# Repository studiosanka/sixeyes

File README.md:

# SixEyes

**A ~S$250 6-DOF robotic arm with 500 g @ 500 mm capability, designed to be built at home.**

SixEyes is an open-source 5-DOF arm plus a gripper, built from 3D-printed cycloidal gearboxes, NEMA17
stepper motors and a hand-solderable PCB. The ~S$250 figure is the whole-arm build budget (prints,
mechanics and electronics; power supply and computer excluded), and 500 g at 500 mm is the design target.

> **Work in progress.** The board design and PCB layout (v1.2) are finished but not yet built or tested. The firmware builds
> but has not run on hardware yet, and the printable parts and build guides are not published yet. Check the
> [status](#status) before you buy anything.

| Front | Back |
|:-:|:-:|
|  |  |

*3D render of the joint board on a NEMA 17 motor (the motor is drawn transparent). Left: the front. Right: the back, with the AS5600 encoder module and the four standoffs that carry the motor. The Super Mini and TMC2209 modules are not shown in their sockets.*

## What you will build

One **Universal Joint PCB** design (ESP32-C6 Super Mini, TMC2209 driver and AS5600 encoder as plug-in or
solder-on modules, fully through-hole) is built four times and linked by a CAN bus:

| Board | Populated | Role |
|---|---|---|
| Base | Stepper 1 driver, USB-C | Bus master, link to your computer |
| Shoulder L | Stepper 2A driver | CAN node |
| Shoulder R | Stepper 2B driver | CAN node, inverse-direction logic |
| Elbow | Stepper 3 driver, 3× servo headers (open-loop) | CAN node, closest to the wrist and gripper |

- **Bus:** CAN at 1 Mbps, a linear chain Base → Shoulder L → Shoulder R → Elbow.
- **Motors:** four NEMA17 (40 mm class) behind 1:25 printed cycloidal reductions. The shoulder uses two
  motors sharing one gearbox.
- **Feedback:** an AS5600 magnetic encoder reads a magnet on each motor shaft.

## Ways to drive the arm

The Base board has two links: **USB** to a computer and **Bluetooth** to a phone. Only one of them is in
control at a time, and the arm says which in every status message. That gives three modes:

| Mode | Who drives | Link | What it is for | Software to use |
|---|---|---|---|---|
| **1. Phone** | Your phone | Bluetooth | Move the gripper by moving your phone; record a movement and replay it, with no computer | [sixeyes-drive](https://github.com/studiosanka/sixeyes-drive) |
| **2. Phone, computer records** | Your phone | Bluetooth for the phone, USB for the computer | Record training data (joint positions and what the phone commanded) while a person teleoperates | [lerobot-sixeyes](https://github.com/studiosanka/lerobot-sixeyes) (listen-only), on top of [sixeyes-host](https://github.com/studiosanka/sixeyes-host) |
| **3. Computer** | A program on your computer | USB | Scripts, motion planning, or a trained AI policy driving the arm | [sixeyes-host](https://github.com/studiosanka/sixeyes-host) (Python), [sixeyes_ros2](https://github.com/studiosanka/sixeyes_ros2) (ROS 2 and MoveIt), [lerobot-sixeyes](https://github.com/studiosanka/lerobot-sixeyes) (LeRobot policy) |

The arm needs no computer for Mode 1. Every tool also has a **practice arm**, so you can try the software
before the hardware is built.

### Software repositories

| Repository | What it is | Used in mode |
|---|---|---|
| [sixeyes-host](https://github.com/studiosanka/sixeyes-host) | The USB protocol (version 1), a Python library, a simulated arm and the `sixeyes-bringup` tool (ports, home, jog, check encoders, monitor). Every other tool builds on it | 2, 3 (and the protocol for 1) |
| [sixeyes-drive](https://github.com/studiosanka/sixeyes-drive) | A web page for Chrome on an Android phone: hold a button and move the phone, record and replay | 1 |
| [lerobot-sixeyes](https://github.com/studiosanka/lerobot-sixeyes) | Plugins for [LeRobot](https://github.com/huggingface/lerobot): record data (Mode 2) and run a policy (Mode 3) | 2, 3 |
| [sixeyes_ros2](https://github.com/studiosanka/sixeyes_ros2) | ROS 2 and MoveIt control, in a mock arm, Gazebo or the real arm | 3 |
| [sixeyes_description](https://github.com/studiosanka/sixeyes_description) | The arm's shape and joint limits (URDF), shared by ROS 2 and the phone page. Placeholder numbers until the CAD is final | 1, 3 |

How the firmware in this repository fits in: it speaks the host protocol on both links
([`firmware/joint_node`](firmware/joint_node/docs/README.md)), arbitrates who is in control, and can store
motions on the arm itself. The Bluetooth service is described there. All of these repositories are
work in progress and **none has run on a real arm yet**; each one's README has its own status table.

## Start here

1. Read the [documentation index](docs/README.md) and follow the numbered guides.
2. The parts list with LCSC part numbers is [`hardware/pcb/bom/v1.2_BOM_LCSC.csv`](hardware/pcb/bom/v1.2_BOM_LCSC.csv).
3. The circuit and wiring are explained in the [PCB design reference](docs/reference/v1.2_PCB_Design_Reference.md).
4. The S$250 claim is checked line by line in the [budget](docs/reference/BUDGET.md).

## Repository map

```
hardware/    PCB (KiCad project, libraries, bill of materials), mechanical files, helper scripts
firmware/    joint_node: the code that runs on the four joint boards
docs/        build guides (start with docs/README.md) and reference documents
```

The software that talks to the arm lives in separate repositories under
[studiosanka](https://github.com/studiosanka); see [Ways to drive the arm](#ways-to-drive-the-arm).

Earlier generations of the project (Alpha and Beta boards, experiments) are kept for reference on the
`archive/dev-2026-10` branch.

## Status

| Part | State |
|---|---|
| Board design v1.2 (circuit, parts list) | ✅ written |
| KiCad schematic and PCB layout | ✅ v1.2 complete (checks clean, not yet built or tested) |
| Manufacturing files (Gerbers) | ✅ v1.2 in [`hardware/pcb/gerbers/`](hardware/pcb/gerbers/) |
| [Budget (S$250 claim)](docs/reference/BUDGET.md) | 🚧 being verified; S$186 priced at average survey prices, S$64 left for the mechanical parts |
| Firmware (`firmware/joint_node`) | 🚧 builds for all four board roles, with the host link, Bluetooth, homing and motion slots; not yet run on hardware |
| Host software (USB, phone, ROS 2, LeRobot) | 🚧 written in [separate repositories](#software-repositories); tested against practice arms only |
| CAN protocol | 🚧 draft |
| 3D-printable parts | ⬜ not yet published |
| Build guides | 🚧 outlines (overview and parts list drafted) |

## Contributing

See [CONTRIBUTING.md](CONTRIBUTING.md) for the usage terms and contribution policy.

## Licence

SixEyes uses three licences:

| | Licence |
|---|---|
| Firmware and software | [Apache 2.0](LICENSE) |
| Hardware designs (KiCad, Gerbers, STL) | [CERN-OHL-S-2.0](hardware/LICENSE) |
| Documentation | [CC-BY-4.0](docs/LICENSE) |

See [CONTRIBUTING.md](CONTRIBUTING.md) for what is required if you manufacture or sell hardware based on these
designs.

## AI assistance

The firmware, software and documentation in this repository were developed with AI assistance from
[Claude](https://www.anthropic.com/claude) (Anthropic) and [GitHub Copilot](https://github.com/features/copilot).
The designs, decisions and review are by the Studio Sanka team.

## Credits

| Role | Contributor |
|---|---|
| Project Lead | Vincent Santosa ([@markantosa](https://github.com/markantosa)) |
| Firmware & System Architecture | Vincent Santosa ([@markantosa](https://github.com/markantosa)) |
| Joint PCB Design (v1) and earlier Follower PCB Design | Vincent Santosa ([@markantosa](https://github.com/markantosa)) |
| Cycloidal Drive Design Lead | Chai ([@sevenovaa](https://github.com/sevenovaa)) |
| Leader PCB Design (Alpha/Beta, archived) | Audrey ([@odriyy](https://github.com/odriyy)) |
| Mechanical Design (cycloidal drive, original design) | Ren Jie ([@trenjie03](https://github.com/trenjie03)) |

## Contact

Bugs and questions: https://github.com/studiosanka/sixeyes/issues

---

Built by [Studio Sanka](https://github.com/studiosanka), a not-for-profit mechatronics design collaborative in
Singapore. **Last updated:** October 2026.

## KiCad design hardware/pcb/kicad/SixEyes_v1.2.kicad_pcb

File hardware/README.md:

# Hardware

Everything needed to build the electronics and the mechanics of the arm.

| Front | Back |
|:-:|:-:|
|  |  |

*3D renders of the joint board on a NEMA 17 motor (the motor is drawn transparent). Left: the front. Right: the back, with the AS5600 encoder module and the four standoffs that carry the motor. The Super Mini and TMC2209 modules are not shown in their sockets.*

| Folder | What is in it | Status |
|---|---|---|
| [`pcb/kicad/`](pcb/kicad/) | KiCad project for the joint board (open `SixEyes_v1.2.kicad_pro`) | ready (v1.2) |
| [`pcb/libraries/`](pcb/libraries/) | Symbols, footprints and 3D models the project uses (nothing to install) | ready |
| [`pcb/bom/`](pcb/bom/) | Bill of materials with LCSC part numbers | ready (v1.2) |
| [`bom/`](bom/) | Bill of materials for the whole arm (quantities and specs, no prices) | electronics ready, mechanical to come |
| [`pcb/drawings/`](pcb/drawings/) | Signed schematic and layout plots (PDF), v1.2 | ready |
| [`pcb/gerbers/`](pcb/gerbers/) | Files to send to a PCB manufacturer | ready (v1.2) |
| [`mechanical/stl/`](mechanical/stl/) | 3D-printable parts | coming soon |
| [`tools/`](tools/) | Scripts that generate the custom KiCad parts | for maintainers |

Open the KiCad project with KiCad 10. The project finds its libraries relative to itself.

The circuit is explained in the [PCB design reference](../docs/reference/v1.2_PCB_Design_Reference.md).

## A note on the tight placement

The components on this board are packed very tightly, and in a few places parts slightly overlap. That is deliberate: the aim was a small board that sits on the back of a NEMA 17 motor, made only of through-hole parts a beginner can solder, and kept neat. KiCad's courtyard checks are switched off for that reason, while every other check (clearance, shorts, hole spacing, edge distance, our own power and CAN rules) is clean. We are sorry if it makes review harder, and we hope you understand. See the [design reference](../docs/reference/v1.2_PCB_Design_Reference.md) for details.

## Licence

Hardware designs are licensed under CERN-OHL-S-2.0, see [LICENSE](LICENSE).

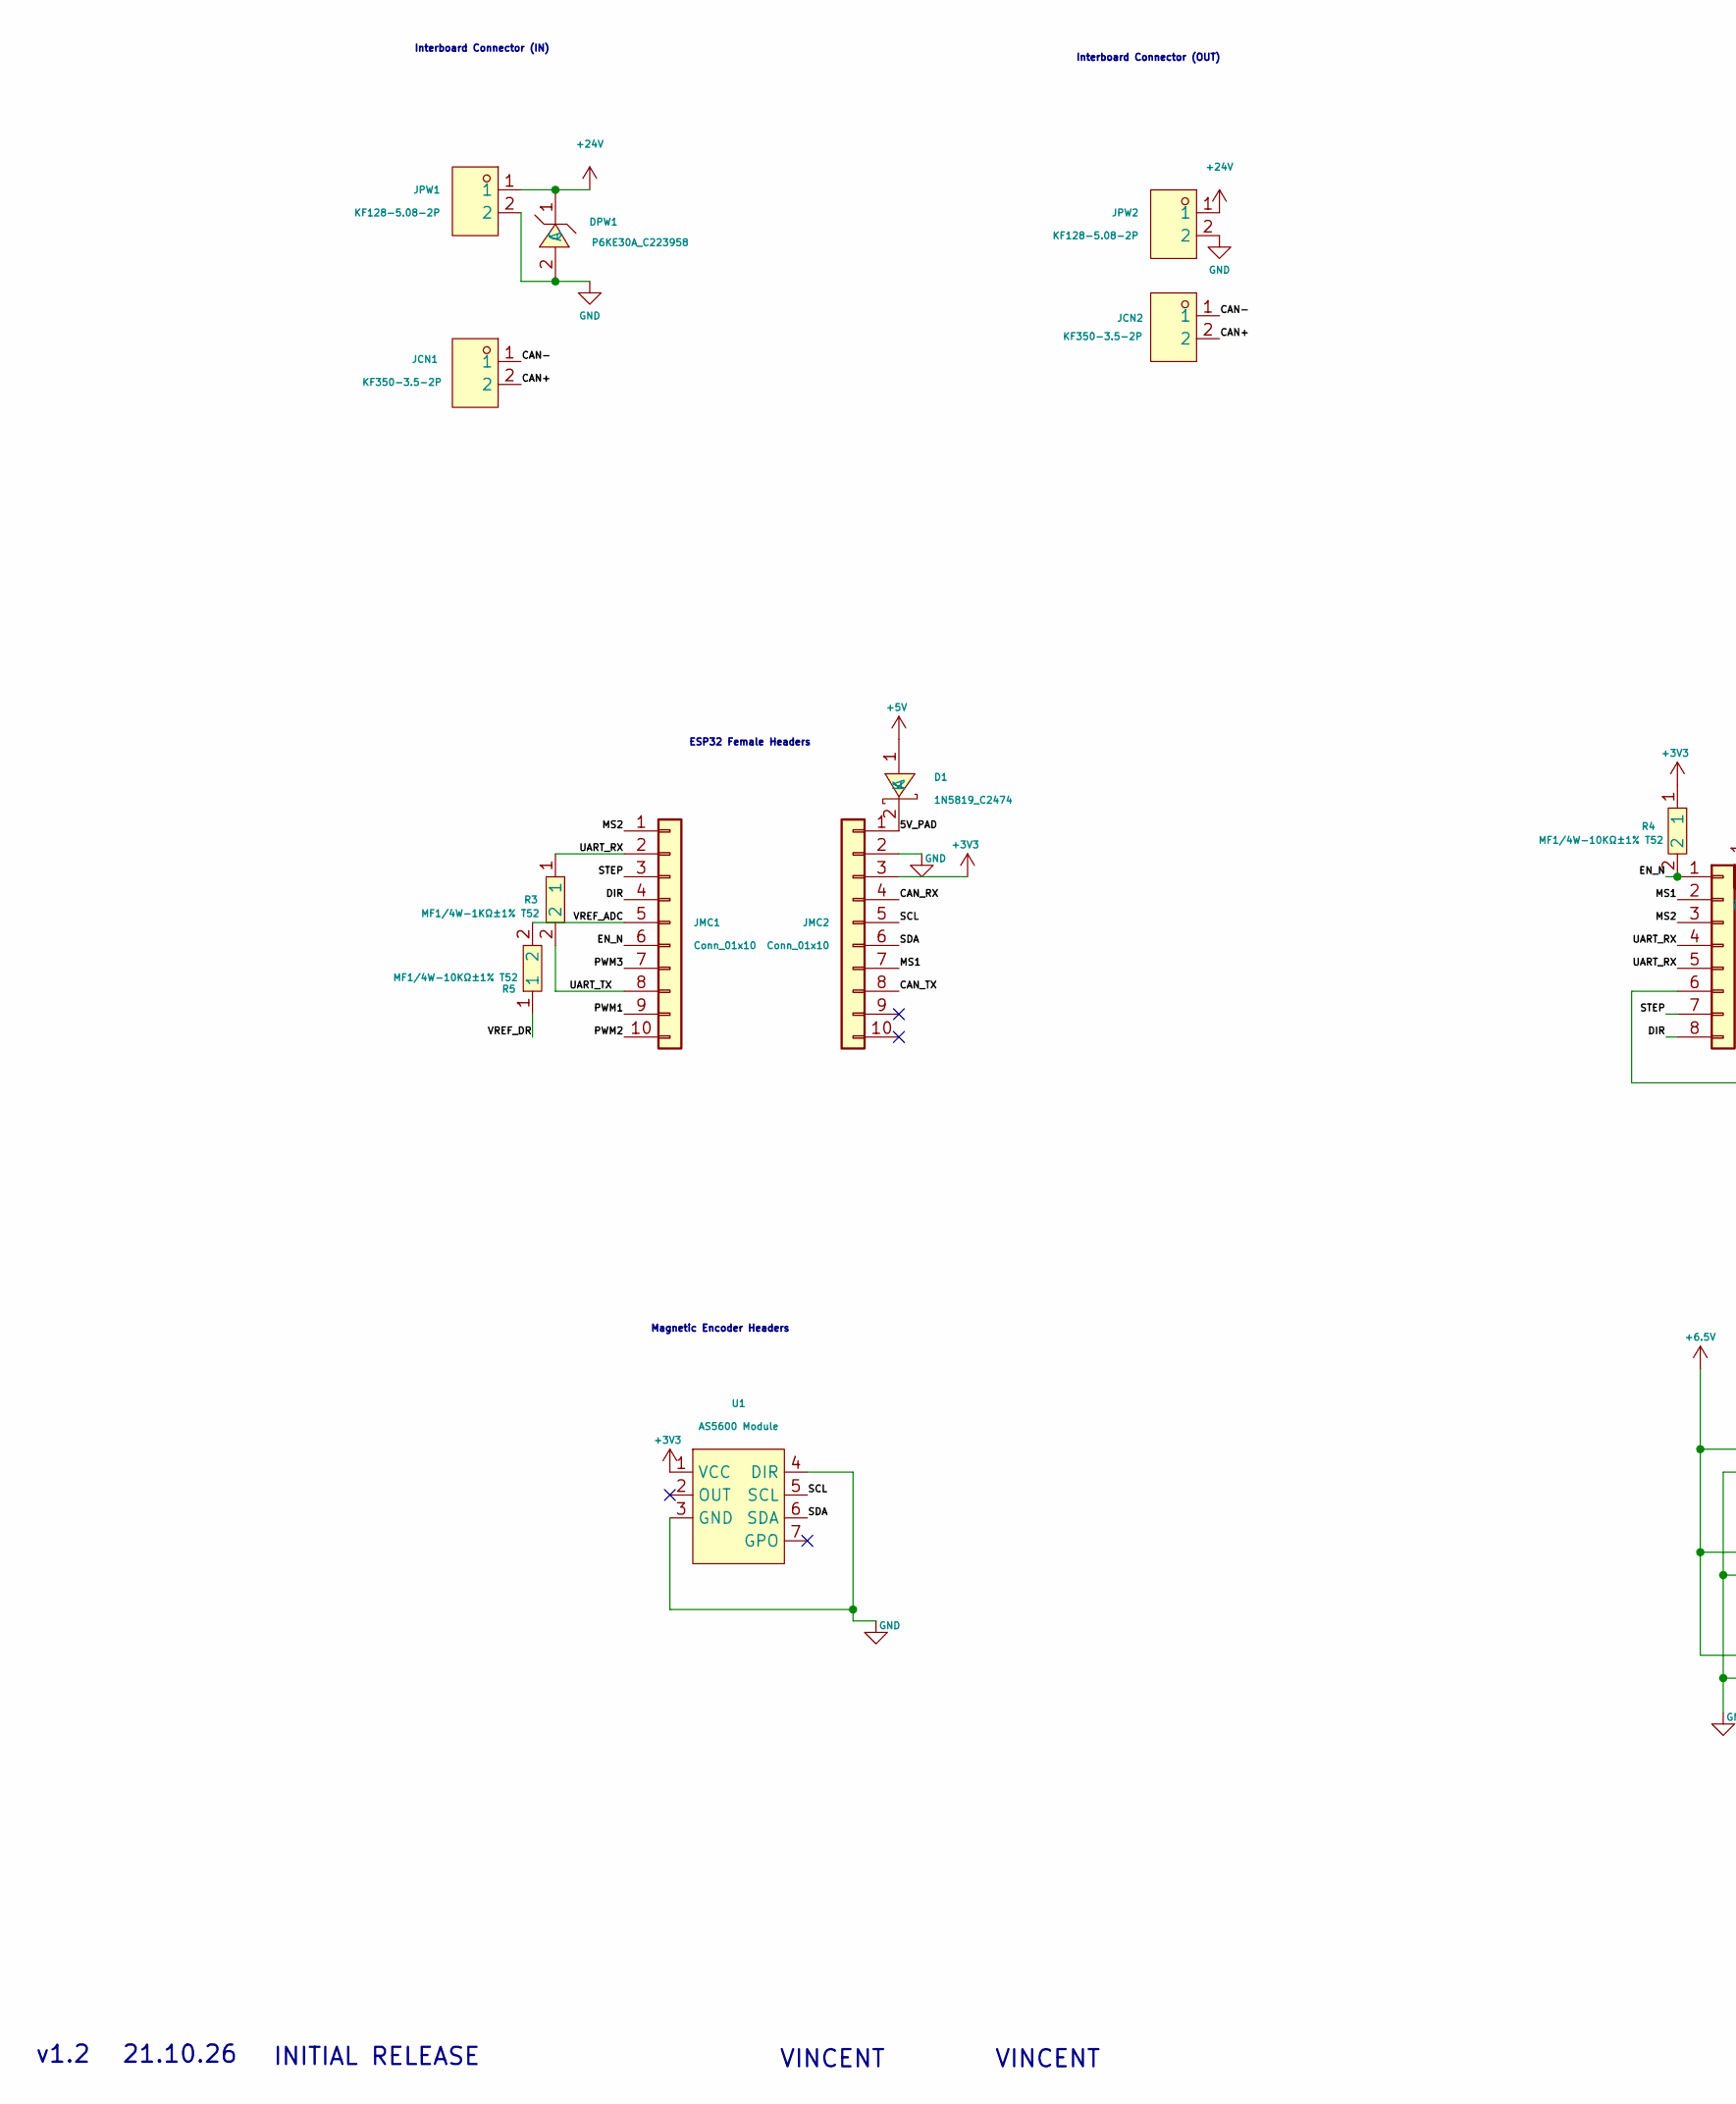
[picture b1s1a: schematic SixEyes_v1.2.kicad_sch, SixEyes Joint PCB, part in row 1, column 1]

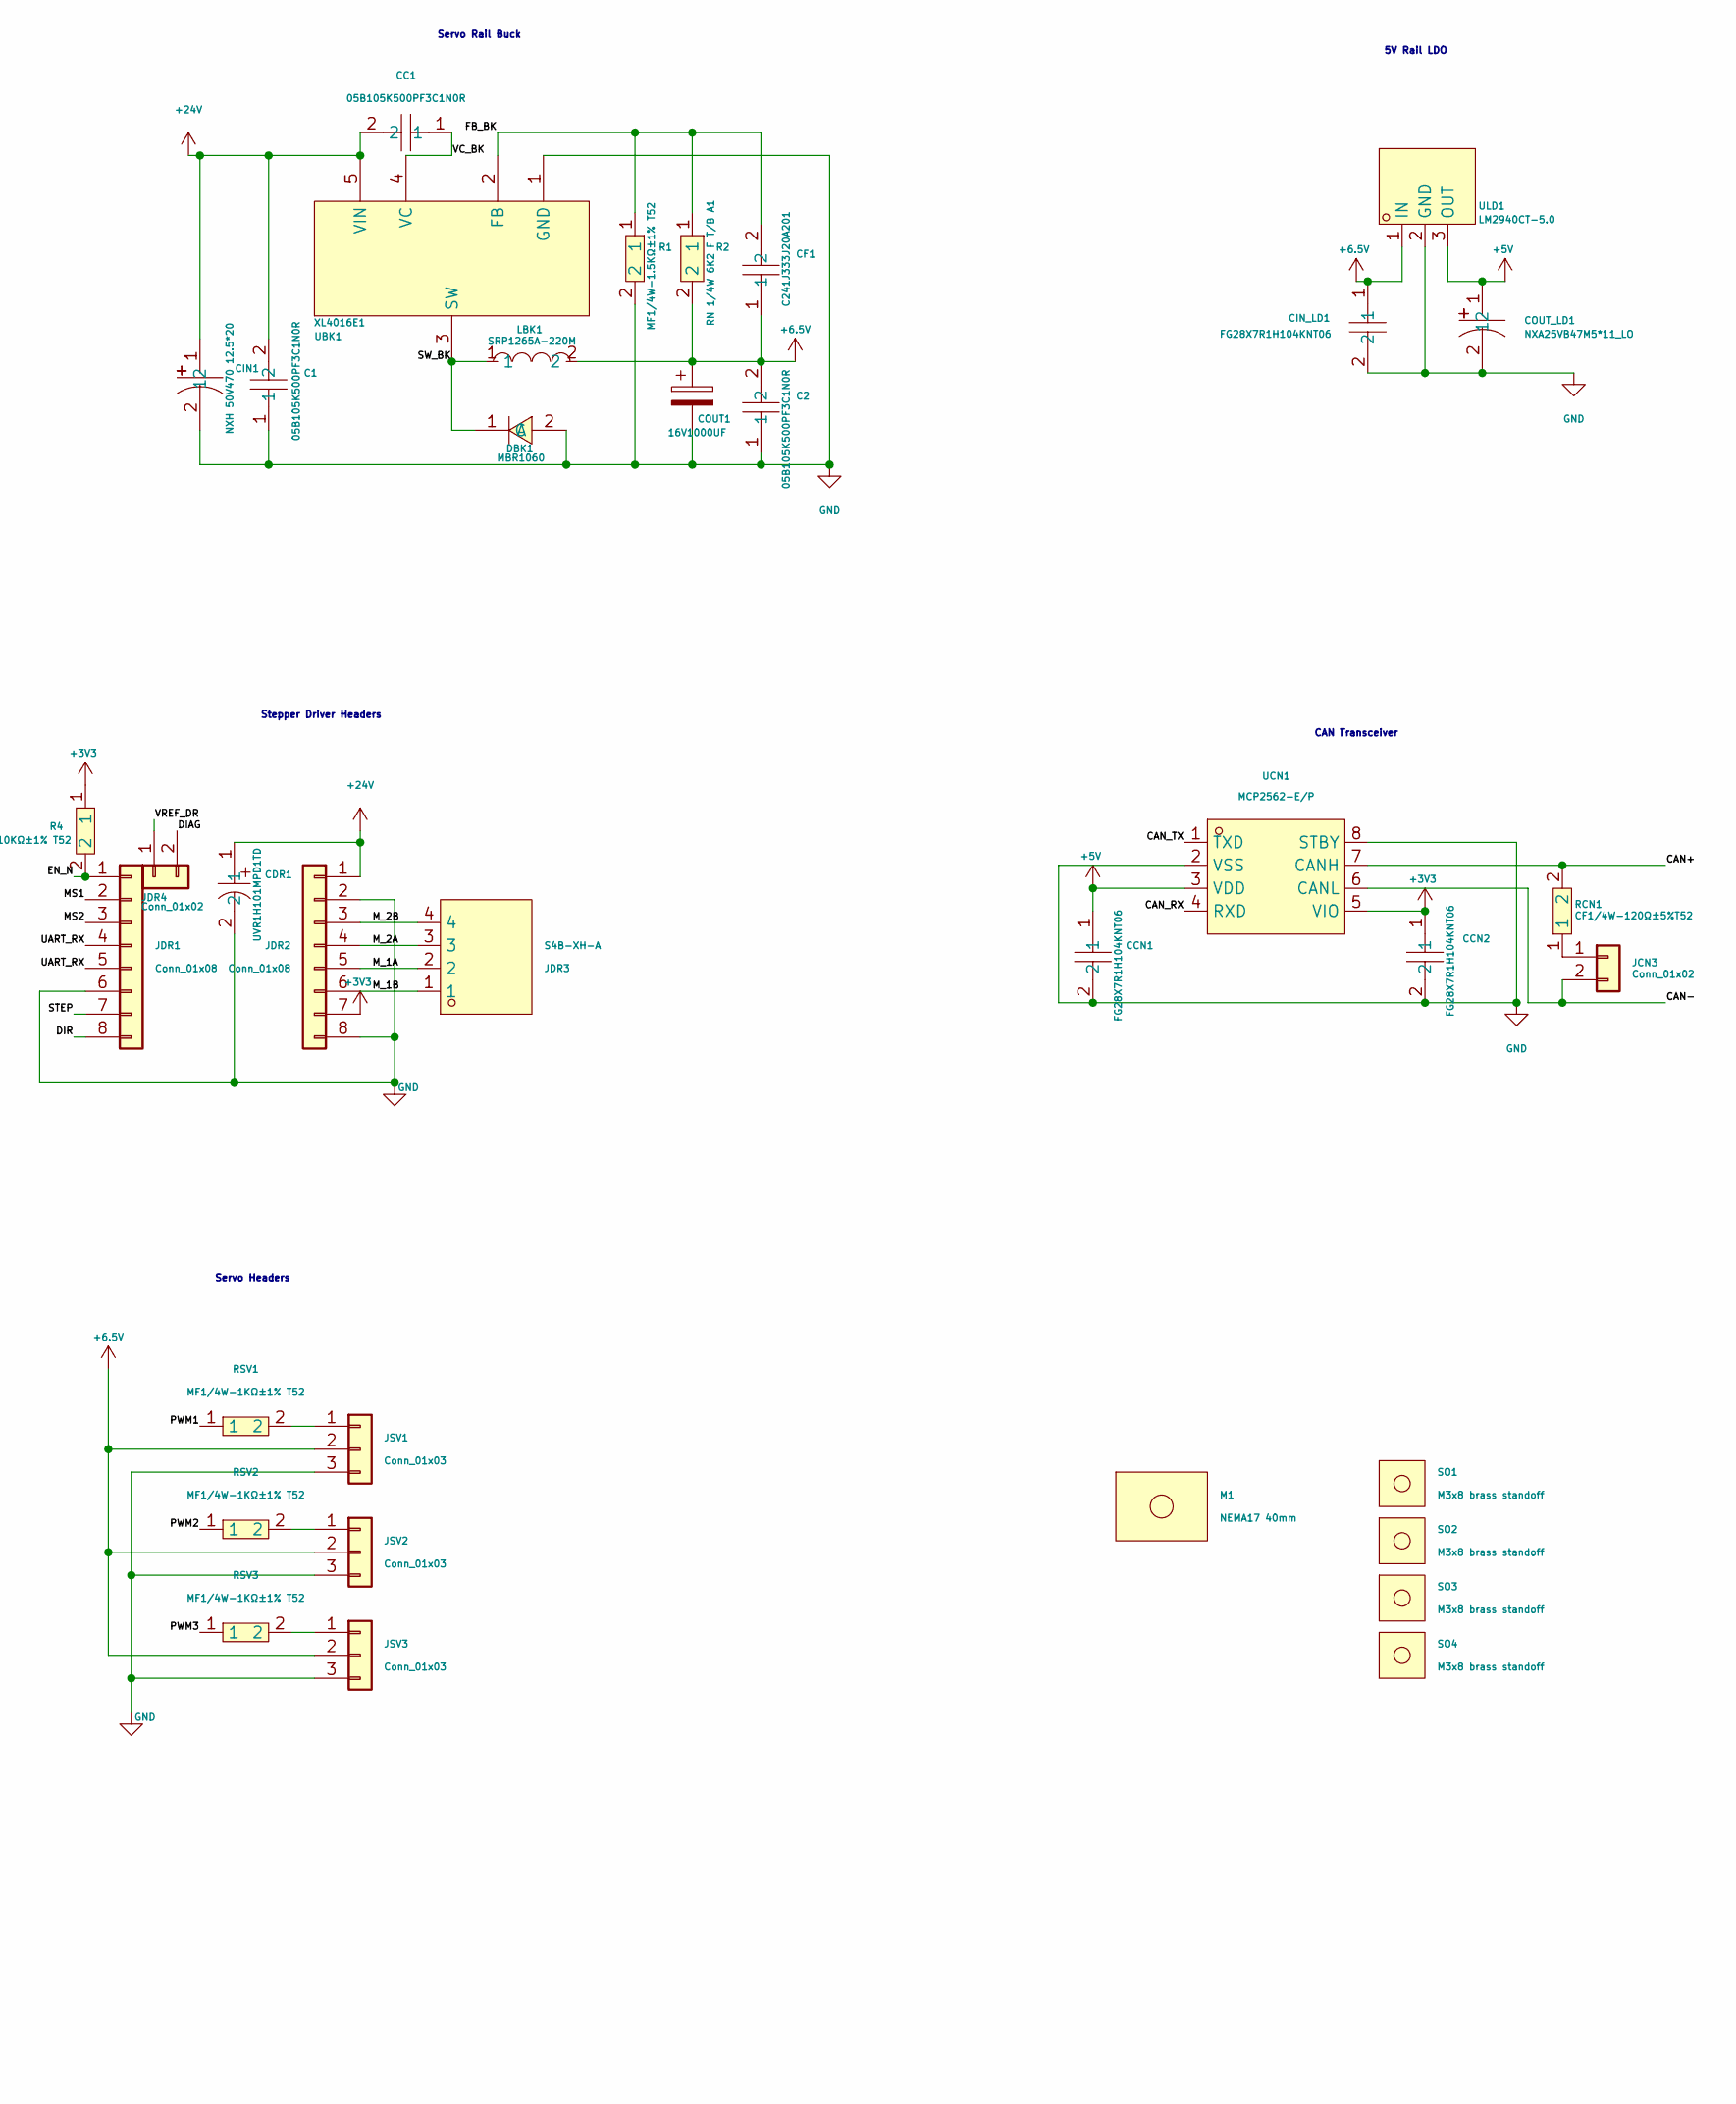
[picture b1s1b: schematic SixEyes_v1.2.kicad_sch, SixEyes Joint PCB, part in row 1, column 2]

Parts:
C1, C2: 05B105K500PF3C1N0R; CAP-TH_L4.2-W3.8-P5.08-D0.5; MPN 05B105K500PF3C1N0R; LCSC Part C409823
CC1: 05B105K500PF3C1N0R; CAP-TH_L4.2-W3.8-P5.08-D0.5; MPN 05B105K500PF3C1N0R; LCSC Part C409823
CCN1, CCN2: FG28X7R1H104KNT06; CAP-TH_L4.0-W2.5-P5.00-D1.0; MPN FG28X7R1H104KNT06; LCSC Part C342794
CDR1: UVR1H101MPD1TD; CAP-TH_BD8.0-P3.50-D0.6-FD; MPN UVR1H101MPD1TD; LCSC Part C1580926
CF1: C241J333J20A201; CAP-TH_L7.2-W2.5-P5.00-D0.6; MPN C241J333J20A201; LCSC Part C401238
CIN1: NXH 50V470 12.5*20; CAP-TH_BD12.5-P5.00-D0.6-FD; MPN NXH 50V470 12.5*20; LCSC Part C165672
CIN_LD1: FG28X7R1H104KNT06; CAP-TH_L4.0-W2.5-P5.00-D1.0; MPN FG28X7R1H104KNT06; LCSC Part C342794
COUT1: 16V1000UF; CP_Radial_D10.0mm_P5.00mm
COUT_LD1: NXA25VB47M5*11_LO; CAP-TH_BD5.0-P2.00-D0.8-FD; MPN NXA25V47M5*11 LO; LCSC Part C346942
D1: 1N5819_C2474; DO-41_BD2.4-L4.7-P8.70-D0.9-FD; MPN 1N5819; LCSC Part C2474
DBK1: MBR1060; TO-220AC_L10.0-W4.5-P5.08-T; MPN MBR1060; LCSC Part C260256
DPW1: P6KE30A_C223958; DO-15_BD3.1-L6.7-P10.70-D0.9-RD; MPN P6KE30A; LCSC Part C223958
JCN1, JCN2: KF350-3.5-2P; CONN-TH_P3.50_KF350-3.5-2P; MPN KF350-3.5-2P; LCSC Part C474892
JCN3: Conn_01x02; PinHeader_1x02_P2.54mm_Vertical
JDR1, JDR2: Conn_01x08; PinSocket_1x08_P2.54mm_Vertical
JDR3: S4B-XH-A; CONN-TH_S4B-XH-A-LF-SN; MPN S4B-XH-A(LF)(SN); LCSC Part C157925
JDR4: Conn_01x02; PinSocket_1x02_P2.54mm_Vertical
JMC1, JMC2: Conn_01x10; PinSocket_1x10_P2.54mm_Vertical
JPW1, JPW2: KF128-5.08-2P; CONN-TH_P5.08_KF128-5.08-2P; MPN KF128-5.08-2P-AA; LCSC Part C474952
JSV1, JSV2, JSV3: Conn_01x03; PinHeader_1x03_P2.54mm_Horizontal
LBK1: SRP1265A-220M; IND-SMD_L12.6-W12.5-SRP1265A-220M; MPN SRP1265A-220M; LCSC Part C2041465
M1: NEMA17 40mm; NEMA17_40mm_Rear_Overhead
R1: MF1/4W-1.5KΩ±1% T52; RES-TH_BD2.3-L6.5-P10.50-D0.5; MPN MF1/4W-1.5KΩ±1% T; LCSC Part C119328
R2: RN 1/4W 6K2 F T/B A1; RES-TH_BD2.4-L6.3-P10.30-D0.6; MPN RN 1/4W 6K2 F T/B A1; LCSC Part C410594
R3: MF1/4W-1KΩ±1% T52; RES-TH_BD2.3-L6.5-P10.50-D0.5; MPN MF1/4W-1KΩ±1% T; LCSC Part C119324
R4, R5: MF1/4W-10KΩ±1% T52; RES-TH_BD2.3-L6.5-P10.50-D0.5; MPN MF1/4W-10KΩ±1% T; LCSC Part C119347
RCN1: CF1/4W-120Ω±5%T52; RES-TH_BD2.3-L6.5-P10.50-D0.5; MPN CF1/4W-120Ω±5%T52; LCSC Part C714282
RSV1, RSV2, RSV3: MF1/4W-1KΩ±1% T52; RES-TH_BD2.3-L6.5-P10.50-D0.5; MPN MF1/4W-1KΩ±1% T; LCSC Part C119324
SO1, SO2, SO3, SO4: M3x8 brass standoff; Standoff_M3_8mm_Hex; MPN M3*8; LCSC Part C551328
U1: AS5600 Module; AS5600_Module_C_Solder_1x3_1x4
UBK1: XL4016E1; TO-220-5L_L10.2-W4.5-P1.71-L; MPN XL4016E1; LCSC Part C55881
UCN1: MCP2562-E/P; PDIP-8_L9.3-W6.4-P2.54-LS7.6-BL; MPN MCP2562-E/P; LCSC Part C640345
ULD1: LM2940CT-5.0; TO-220-3_L10.0-W4.5-P2.54-L; MPN LM2940CT-5.0/NOPB; LCSC Part C9413

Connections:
+3V3: CCN2.1, JDR2.7, JMC2.3, R4.1, U1.1 (VCC), UCN1.5 (VIO)
+5V: CCN1.1, COUT_LD1.1, D1.1 (A), UCN1.3 (VDD), ULD1.3 (OUT)
+6.5V: C2.2, CF1.1, CIN_LD1.1, COUT1.1, JSV1.2, JSV2.2, JSV3.2, LBK1.2, R2.2, ULD1.1 (IN)
+24V: C1.2, CC1.2, CDR1.1, CIN1.1, DPW1.1 (C), JDR2.1, JPW1.1, JPW2.1, UBK1.5 (VIN)
/5V_PAD: D1.2 (K), JMC2.1
/CAN+: JCN1.2, JCN2.2, RCN1.2, UCN1.7 (CANH)
/CAN-: JCN1.1, JCN2.1, JCN3.2, UCN1.6 (CANL)
/CAN_RX: JMC2.4, UCN1.4 (RXD)
/CAN_TX: JMC2.8, UCN1.1 (TXD)
/DIAG: JDR4.2
/DIR: JDR1.8, JMC1.4
/EN_N: JDR1.1, JMC1.6, R4.2
/FB_BK: CF1.2, R1.1, R2.1, UBK1.2 (FB)
/MS1: JDR1.2, JMC2.7
/MS2: JDR1.3, JMC1.1
/M_1A: JDR2.5, JDR3.2
/M_1B: JDR2.6, JDR3.1
/M_2A: JDR2.4, JDR3.3
/M_2B: JDR2.3, JDR3.4
/PWM1: JMC1.9, RSV1.1
/PWM2: JMC1.10, RSV2.1
/PWM3: JMC1.7, RSV3.1
/SCL: JMC2.5, U1.5 (SCL)
/SDA: JMC2.6, U1.6 (SDA)
/STEP: JDR1.7, JMC1.3
/SW_BK: DBK1.1 (C), LBK1.1, UBK1.3 (SW)
/UART_RX: JDR1.4, JDR1.5, JMC1.2, R3.1
/UART_TX: JMC1.8, R3.2
/VC_BK: CC1.1, UBK1.4 (VC)
/VREF_ADC: JMC1.5, R5.2
/VREF_DR: JDR4.1, R5.1
GND: C1.1, C2.1, CCN1.2, CCN2.2, CDR1.2, CIN1.2, CIN_LD1.2, COUT1.2, COUT_LD1.2, DBK1.2 (A), DPW1.2 (A), JDR1.6, JDR2.2, JDR2.8, JMC2.2, JPW1.2, JPW2.2, JSV1.3, JSV2.3, JSV3.3, R1.2, U1.3 (GND), U1.4 (DIR), UBK1.1 (GND), UCN1.2 (VSS), UCN1.8 (STBY), ULD1.2 (GND)
unnamed: JCN3.1, RCN1.1
unnamed: JSV1.1, RSV1.2
unnamed: JSV2.1, RSV2.2
unnamed: JSV3.1, RSV3.2

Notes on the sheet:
INITIAL RELEASE
Servo Rail Buck
VINCENT
5V Rail LDO
Servo Headers
Stepper Driver Headers
Interboard Connector (IN)
Magnetic Encoder Headers
21.10.26
Interboard Connector (OUT)
ESP32 Female Headers
CAN Transceiver
v1.2

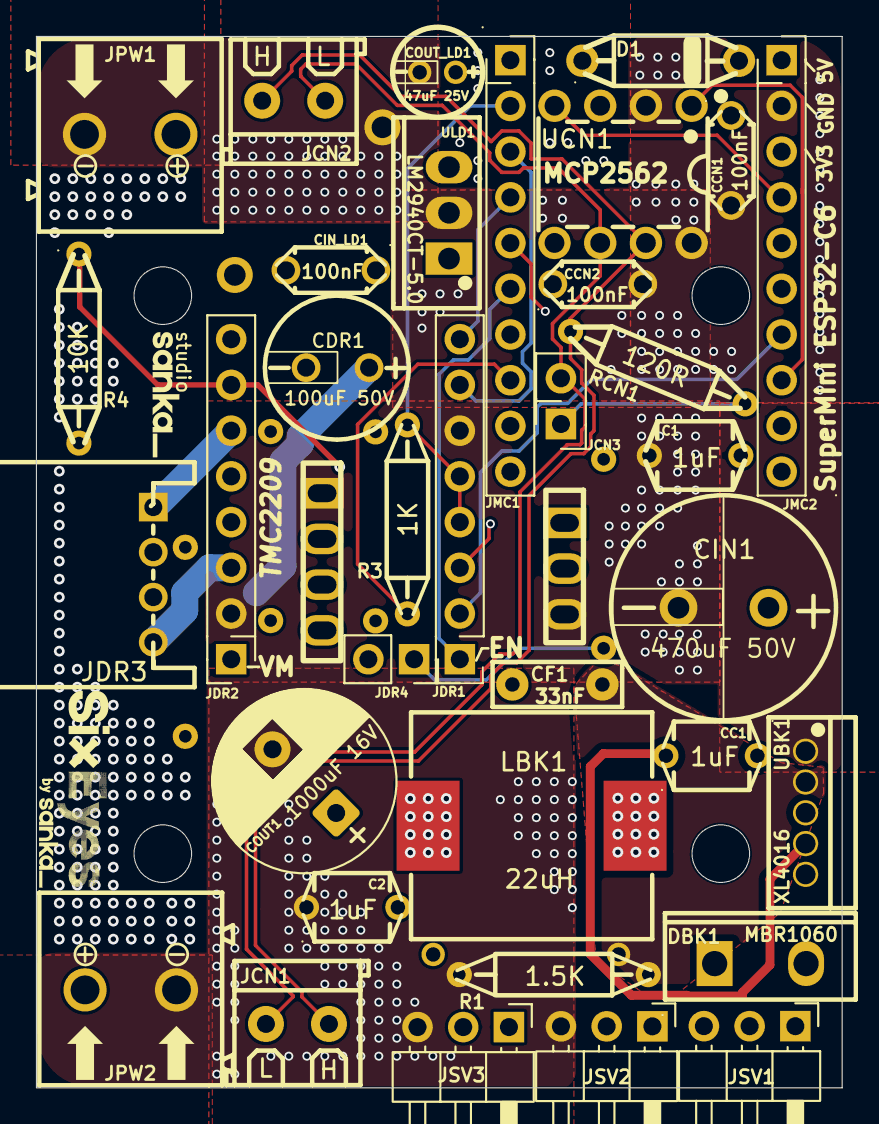
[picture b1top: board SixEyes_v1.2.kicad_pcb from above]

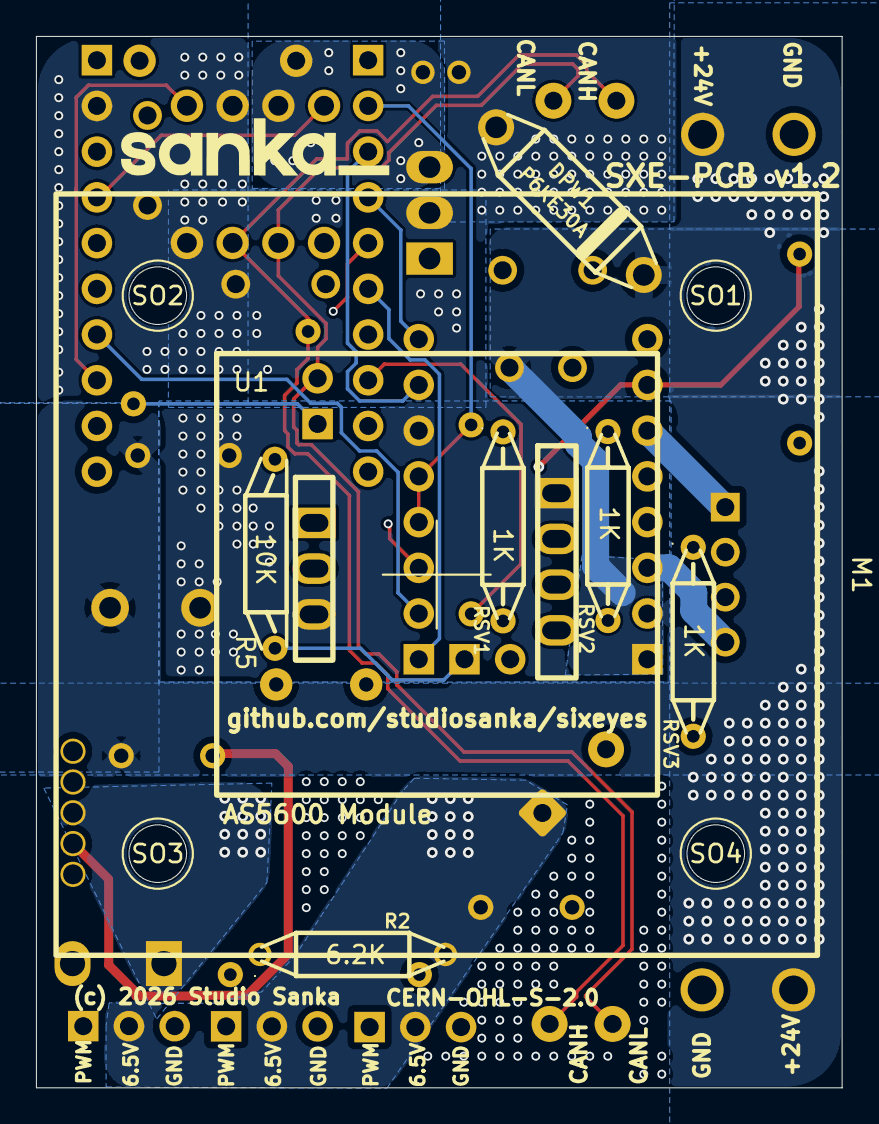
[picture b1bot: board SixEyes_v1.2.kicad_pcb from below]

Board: 4 copper layers, 44.8 x 58.4 mm, 47 parts (12 on the bottom side), 35 nets.

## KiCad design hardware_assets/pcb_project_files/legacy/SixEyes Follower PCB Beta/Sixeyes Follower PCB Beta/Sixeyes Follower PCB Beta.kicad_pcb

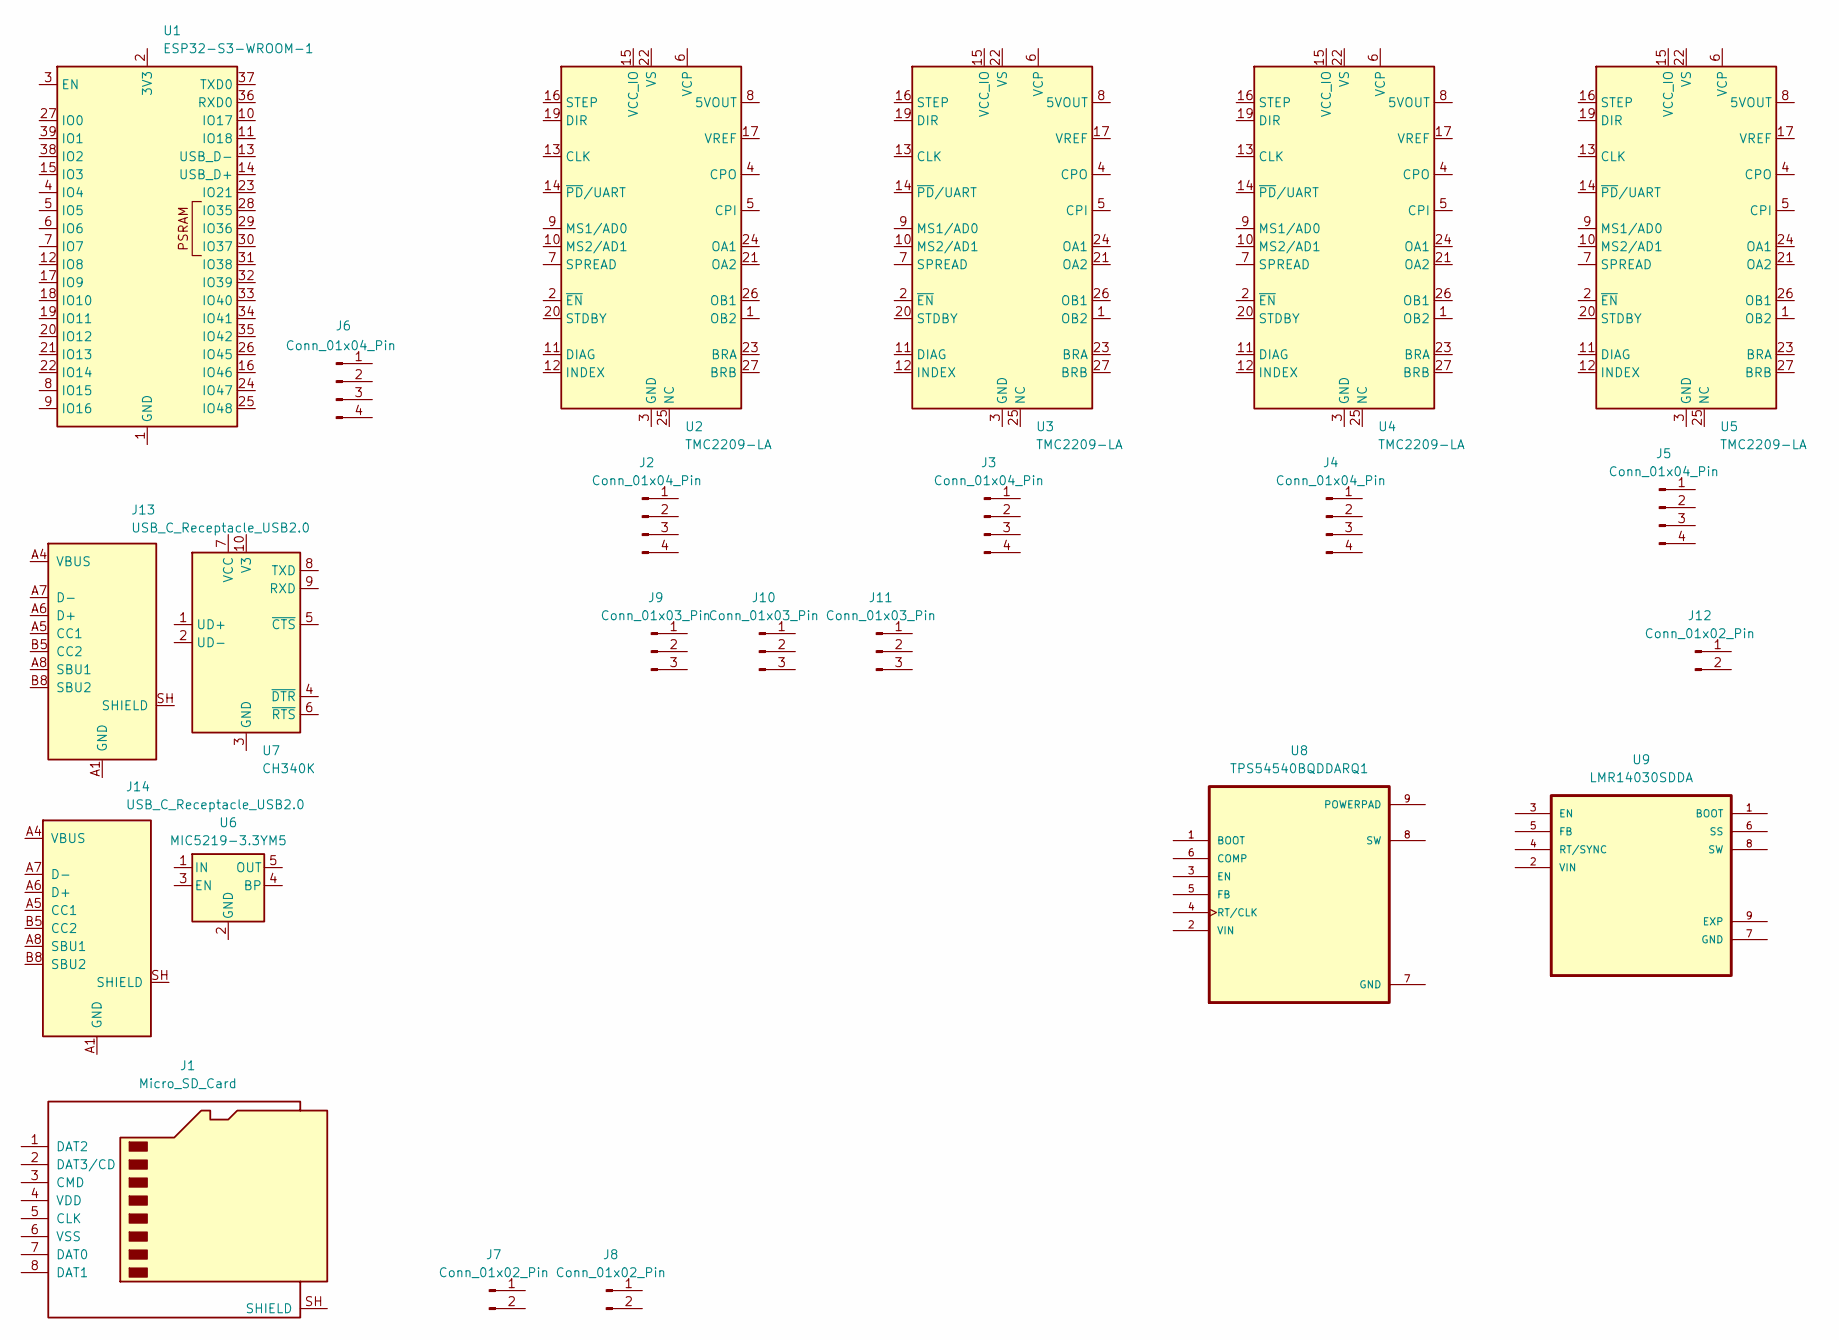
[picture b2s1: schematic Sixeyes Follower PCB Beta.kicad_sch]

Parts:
J1: Micro_SD_Card; microSD_HC_Hirose_DM3D-SF
J2, J3, J4, J5, J6: Conn_01x04_Pin; JST_XH_B4B-XH-A_1x04_P2.50mm_Vertical
J7, J8: Conn_01x02_Pin; JST_XH_B2B-XH-A_1x02_P2.50mm_Vertical
J9, J10, J11: Conn_01x03_Pin; JST_XH_B3B-XH-A_1x03_P2.50mm_Vertical
J12: Conn_01x02_Pin; AMASS_XT30U-M_1x02_P5.0mm_Vertical
J13, J14: USB_C_Receptacle_USB2.0; USB_C_Receptacle_HRO_TYPE-C-31-M-12
U1: ESP32-S3-WROOM-1
U2, U3, U4, U5: TMC2209-LA; VQFN-28-1EP_5x5mm_P0.5mm_EP3.7x3.7mm_ThermalVias
U6: MIC5219-3.3YM5; SOT-23-5
U7: CH340K; SSOP-10-1EP_3.9x4.9mm_P1mm_EP2.1x3.3mm
U8: TPS54540BQDDARQ1; VREG_LM5017MR_NOPB
U9: LMR14030SDDA; VREG_LM5017MR_NOPB

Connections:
unnamed: U1.1 (GND), U1.40 (GND), U1.41 (GND)
unnamed: U2.3 (GND), U2.18 (GND), U2.29 (GND)
unnamed: U2.22 (VS), U2.28 (VS)
unnamed: U3.3 (GND), U3.18 (GND), U3.29 (GND)
unnamed: U3.22 (VS), U3.28 (VS)
unnamed: U4.3 (GND), U4.18 (GND), U4.29 (GND)
unnamed: U4.22 (VS), U4.28 (VS)
unnamed: U5.3 (GND), U5.18 (GND), U5.29 (GND)
unnamed: U5.22 (VS), U5.28 (VS)
unnamed: U7.3 (GND), U7.11 (GND)
unnamed: U9.9 (EXP), U9.V1 (EXP), U9.V2 (EXP), U9.V3 (EXP), U9.V4 (EXP), U9.V5 (EXP), U9.V6 (EXP)

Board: 2 copper layers, 22 parts (0 on the bottom side), 10 nets, no tracks yet.

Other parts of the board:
sanka: LOGO; sanka2

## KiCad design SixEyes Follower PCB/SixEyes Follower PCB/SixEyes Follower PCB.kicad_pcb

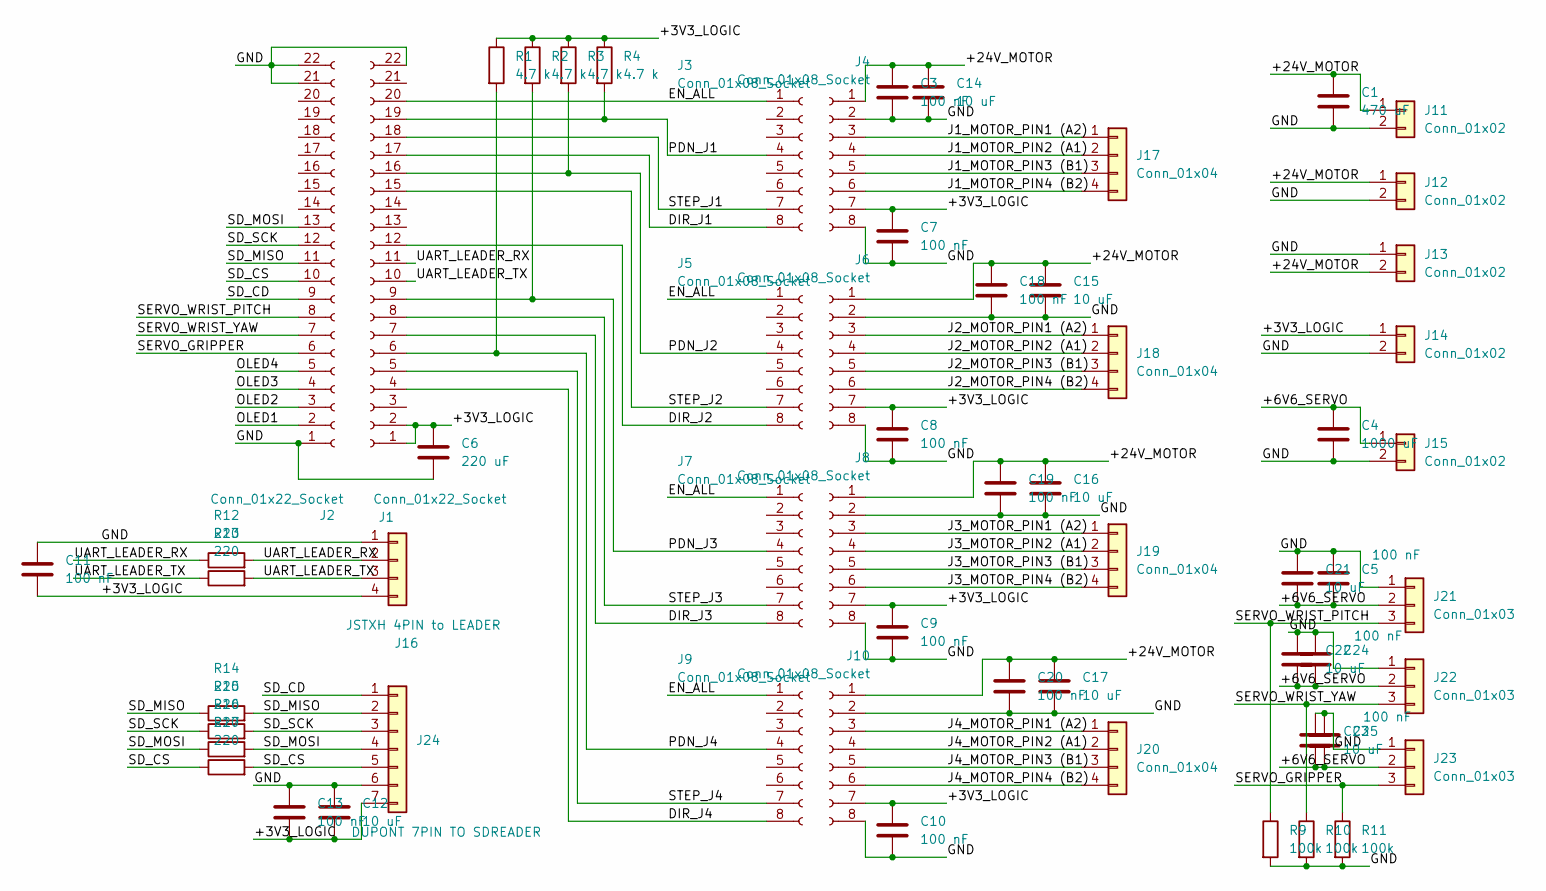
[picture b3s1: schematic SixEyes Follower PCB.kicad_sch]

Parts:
C1: 470 uF; CP_Radial_D10.0mm_P5.00mm
C3, C5, C7, C8, C9, C10, C11, C13, C18, C19, C20, C24, C25: 100 nF; C_Disc_D5.0mm_W2.5mm_P5.00mm
C4: 1000 uF; CP_Radial_D10.0mm_P5.00mm
C6: 220 uF; C_Disc_D5.0mm_W2.5mm_P5.00mm
C12, C14, C15, C16, C17, C21, C22, C23: 10 uF; CP_Radial_D8.0mm_P3.50mm
J1, J2: Conn_01x22_Socket; PinSocket_1x22_P2.54mm_Vertical
J3, J4, J5, J6, J7, J8, J9, J10: Conn_01x08_Socket; PinSocket_1x08_P2.54mm_Vertical
J11, J12, J13, J14, J15: Conn_01x02; TerminalBlock_Phoenix_MKDS-1,5-2_1x02_P5.00mm_Horizontal
J16: JSTXH 4PIN to LEADER; JST_XH_B4B-XH-A_1x04_P2.50mm_Vertical
J17, J18, J19, J20: Conn_01x04; JST_XH_B4B-XH-A_1x04_P2.50mm_Vertical
J21, J22, J23: Conn_01x03; JST_XH_B3B-XH-A_1x03_P2.50mm_Vertical
J24: DUPONT 7PIN TO SDREADER; PinSocket_1x07_P2.54mm_Vertical
R1, R2, R3, R4: 4.7 k; R_Axial_DIN0207_L6.3mm_D2.5mm_P7.62mm_Horizontal
R9, R10, R11: 100k; R_Axial_DIN0207_L6.3mm_D2.5mm_P7.62mm_Horizontal
R12, R13, R14, R15, R16, R17: 220; R_Axial_DIN0207_L6.3mm_D2.5mm_P7.62mm_Horizontal

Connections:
/+3V3_LOGIC: C6.1, C7.1, C8.1, C9.1, C10.1, C11.2, C12.2, C13.2, J1.1 (3V3), J1.2, J4.7, J6.7, J8.7, J10.7, J14.1, J16.4, J24.7, R1.1, R2.1, R3.1, R4.1
/+6V6_SERVO: C4.1, C5.2, C21.2, C22.2, C23.2, C24.2, C25.2, J15.1, J21.2, J22.2, J23.2
/+24V_MOTOR: C1.1, C3.1, C14.1, C15.1, C16.1, C17.1, C18.1, C19.1, C20.1, J4.1, J6.1, J8.1, J10.1, J11.1, J12.1, J13.2
/DIR_J1: J1.17, J3.8
/DIR_J2: J1.12, J5.8
/DIR_J3: J1.7, J7.8
/DIR_J4: J1.4, J9.8
/EN_ALL: J1.20, J3.1, J5.1, J7.1, J9.1
/GND: C1.2, C3.2, C4.2, C5.1, C6.2, C7.2, C8.2, C9.2, C10.2, C11.1, C12.1, C13.1, C14.2, C15.2, C16.2, C17.2, C18.2, C19.2, C20.2, C21.1, C22.1, C23.1, C24.1, C25.1, J1.22, J2.1, J2.21, J2.22, J4.2, J4.8, J6.2, J6.8, J8.2, J8.8, J10.2, J10.8, J11.2, J12.2, J13.1, J14.2, J15.2, J16.1, J21.1, J22.1, J23.1, J24.6, R9.2, R10.2, R11.2
/J1_MOTOR_PIN1 (A2): J4.3, J17.1
/J1_MOTOR_PIN2 (A1): J4.4, J17.2
/J1_MOTOR_PIN3 (B1): J4.5, J17.3
/J1_MOTOR_PIN4 (B2): J4.6, J17.4
/J2_MOTOR_PIN1 (A2): J6.3, J18.1
/J2_MOTOR_PIN2 (A1): J6.4, J18.2
/J2_MOTOR_PIN3 (B1): J6.5, J18.3
/J2_MOTOR_PIN4 (B2): J6.6, J18.4
/J3_MOTOR_PIN1 (A2): J8.3, J19.1
/J3_MOTOR_PIN2 (A1): J8.4, J19.2
/J3_MOTOR_PIN3 (B1): J8.5, J19.3
/J3_MOTOR_PIN4 (B2): J8.6, J19.4
/J4_MOTOR_PIN1 (A2): J10.3, J20.1
/J4_MOTOR_PIN2 (A1): J10.4, J20.2
/J4_MOTOR_PIN3 (B1): J10.5, J20.3
/J4_MOTOR_PIN4 (B2): J10.6, J20.4
/OLED1: J2.2
/OLED2: J2.3
/OLED3: J2.4
/OLED4: J2.5
/PDN_J1: J1.19, J3.4, R4.2
/PDN_J2: J1.16, J5.4, R3.2
/PDN_J3: J1.9, J7.4, R2.2
/PDN_J4: J1.6, J9.4, R1.2
/SD_CD: J2.9, J24.1
/SD_CS: J2.10, J24.5, R17.1, R17.2
/SD_MISO: J2.11, J24.2, R14.1, R14.2
/SD_MOSI: J2.13, J24.4, R16.1, R16.2
/SD_SCK: J2.12, J24.3, R15.1, R15.2
/SERVO_GRIPPER: J2.6, J23.3, R11.1
/SERVO_WRIST_PITCH: J2.8, J21.3, R9.1
/SERVO_WRIST_YAW: J2.7, J22.3, R10.1
/STEP_J1: J1.18, J3.7
/STEP_J2: J1.15, J5.7
/STEP_J3: J1.8, J7.7
/STEP_J4: J1.5, J9.7
/UART_LEADER_RX: J1.11, J16.2, R12.1, R12.2
/UART_LEADER_TX: J1.10, J16.3, R13.1, R13.2

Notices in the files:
hardware/pcb/kicad/SixEyes_v1.2.kicad_pcb:
(c) 2026 Studio Sanka
